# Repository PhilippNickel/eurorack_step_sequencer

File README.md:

# eurorack_step_sequencer
Open Hardware 8 Channel Eurorack Step Sequencer
# Introduction
These are the KiCad PCB files for a DIY eurorack 8 channel step sequencer module. The heart of the system is an Atmega16A and it features a small i2c OLED Display to modify certain settings. The manufacturing, firmware and testing are still work in progress, photos, videos and firmware will follow.
# 3d Model

# Schematic

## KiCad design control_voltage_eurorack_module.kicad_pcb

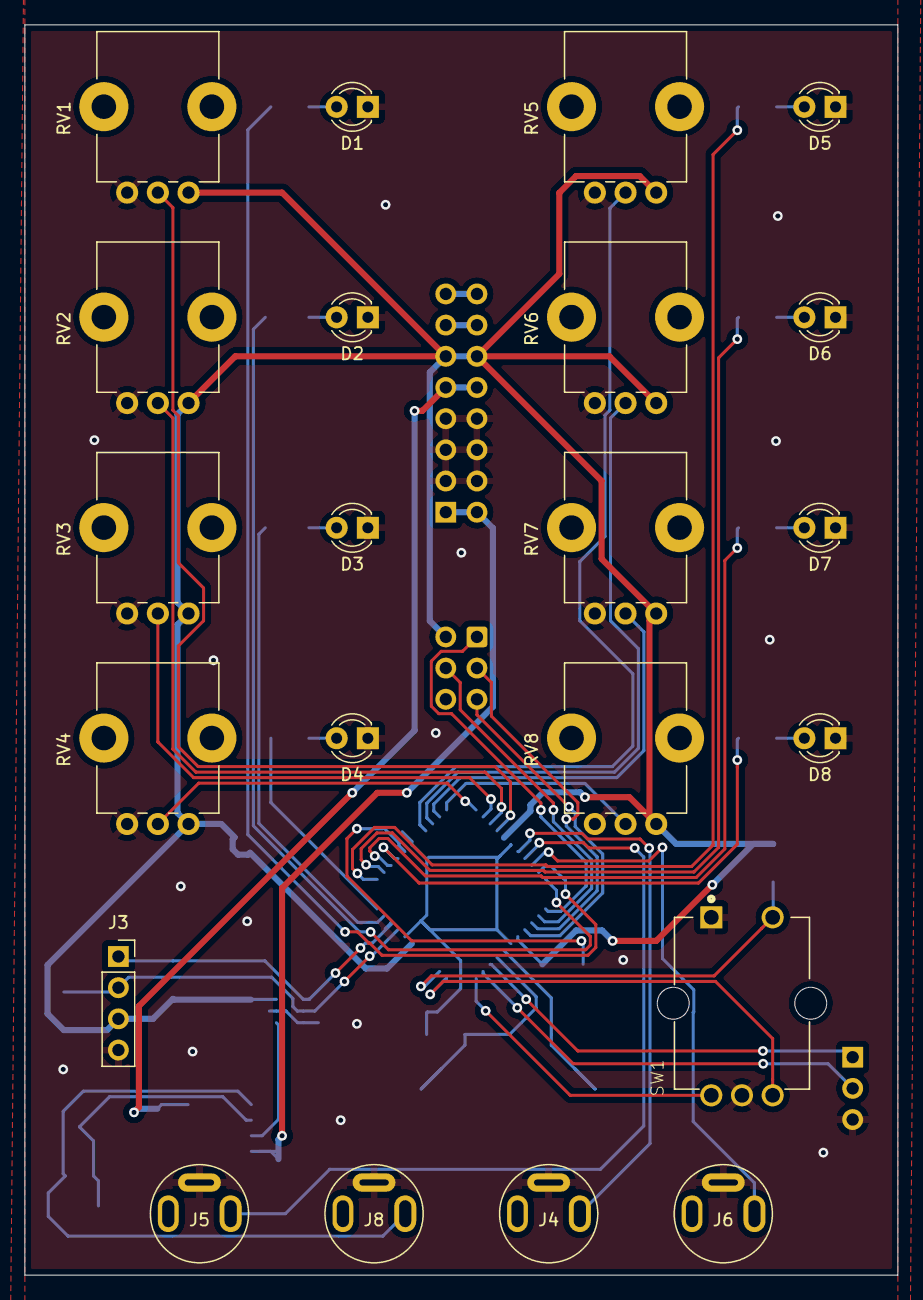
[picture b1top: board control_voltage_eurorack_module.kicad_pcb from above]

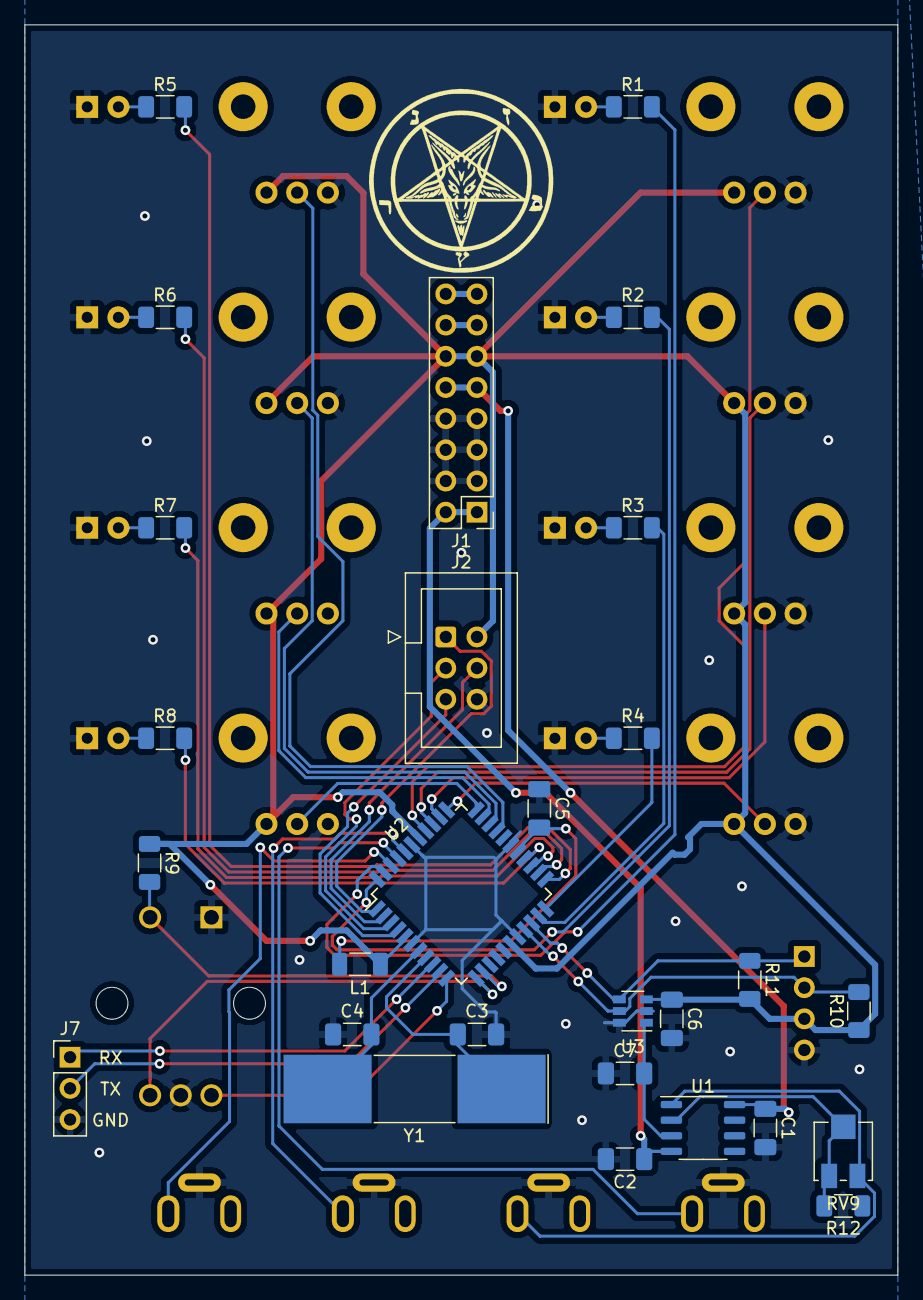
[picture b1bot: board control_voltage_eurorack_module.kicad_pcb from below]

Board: 2 copper layers, 71.1 x 101.9 mm, 50 parts (28 on the bottom side), 50 nets.

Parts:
C1, C2, C5, C6, C7: 100n; C_1206_3216Metric_Pad1.33x1.80mm_HandSolder
C3, C4: 20p; C_1206_3216Metric_Pad1.33x1.80mm_HandSolder
D1, D2, D3, D4, D5, D6, D7, D8: LED; LED_D3.0mm
J1: Conn_02x08_Odd_Even; PinHeader_2x08_P2.54mm_Vertical
J2: AVR-ISP-6; IDC-Header_2x03_P2.54mm_Vertical
J3: Conn_01x04; PinSocket_1x04_P2.54mm_Vertical
J4: TrigOut; Jack_3.5mm_VERTICAL
J5: GateOut; Jack_3.5mm_VERTICAL
J6: ExtClkIn; Jack_3.5mm_VERTICAL
J7: Conn_01x03; PinHeader_1x03_P2.54mm_Vertical
J8: CVOut; Jack_3.5mm_VERTICAL
L1: 10u; L_1206_3216Metric_Pad1.22x1.90mm_HandSolder
R1, R2, R3, R4, R5, R6, R7, R8: 200; R_1206_3216Metric_Pad1.30x1.75mm_HandSolder
R9, R10, R11: 10k; R_1206_3216Metric_Pad1.30x1.75mm_HandSolder
R12: 75k; R_1206_3216Metric_Pad1.30x1.75mm_HandSolder
RV1, RV2, RV3, RV4, RV5, RV6, RV7, RV8: R_POT; Potentiometer_Bourns_PTV09A-1_Single_Vertical
RV9: 100k; Potentiometer_Bourns_3314J_Vertical
SW1: Menu_Encoder; ENC_PEC12R-4025F-S0024
U1: TL072; SO-8_3.9x4.9mm_P1.27mm
U2: ATmega16A-AU; TQFP-44_10x10mm_P0.8mm
U3: MCP4725xxx-xCH; SOT-23-6
Y1: 16M; Crystal_SMD_SeikoEpson_MA505-2Pin_12.7x5.1mm_HandSoldering

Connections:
+5V: C6.1, J1.11, J1.12, J2.2, J3.3, L1.1, R9.1, R10.1, R11.2, RV1.1, RV2.1, RV3.1, RV4.1, RV5.1, RV6.1, RV7.1, RV8.1, U2.5, U2.17, U2.38, U3.3
+12V: C1.1, J1.9, J1.10, U1.8
-12V: C2.1, J1.1, J1.2, U1.4
CV: J1.15, J1.16
GND: C1.2, C2.2, C3.2, C4.2, C5.1, C6.2, C7.1, D1.1, D2.1, D3.1, D4.1, D5.1, D6.1, D7.1, D8.1, J1.3, J1.4, J1.5, J1.6, J1.7, J1.8, J2.6, J3.4, J4.S, J5.S, J6.S, J7.3, J8.S, R12.1, RV1.3, RV2.3, RV3.3, RV4.3, RV5.3, RV6.3, RV7.3, RV8.3, SW1.C, SW1.S1, U2.6, U2.18, U2.28, U2.39, U3.2, U3.6
Gate: J1.13, J1.14
LED0: R1.2, U2.43
LED1: R2.2, U2.44
LED2: R3.2, U2.21
LED3: R4.2, U2.22
LED4: R5.2, U2.23
LED5: R6.2, U2.24
LED6: R7.2, U2.25
LED7: R8.2, U2.26
MISO: J2.1, U2.1
MOSI: J2.4, U2.2
unnamed: C3.1, U2.8, Y1.1
unnamed: C4.1, U2.7, Y1.2
unnamed: C5.2, L1.2, U2.27
unnamed: C7.2, U1.3, U3.1
unnamed: D1.2, R1.1
unnamed: D2.2, R2.1
unnamed: D3.2, R3.1
unnamed: D4.2, R4.1
unnamed: D5.2, R5.1
unnamed: D6.2, R6.1
unnamed: D7.2, R7.1
unnamed: D8.2, R8.1
unnamed: J4.T, U2.40
unnamed: J5.T, U2.41
unnamed: J6.T, U2.42
unnamed: J8.T, RV9.3, U1.1
unnamed: R9.2, SW1.S2, U2.13
unnamed: R12.2, RV9.1, RV9.2, U1.2
unnamed: SW1.A, U2.11
unnamed: SW1.B, U2.12
Pot0: RV1.2, U2.37
Pot1: RV2.2, U2.36
Pot2: RV3.2, U2.35
Pot3: RV4.2, U2.34
Pot4: RV5.2, U2.30
Pot5: RV6.2, U2.31
Pot6: RV7.2, U2.32
Pot7: RV8.2, U2.33
RXD: J7.1, U2.9
Rst: J2.5, U2.4
SCK: J2.3, U2.3
SCL: J3.2, R10.2, U2.19, U3.5
SDA: J3.1, R11.1, U2.20, U3.4
TXD: J7.2, U2.10

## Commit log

2021-03-23 removed .zip from repo
2021-03-28 fixed wrong i2c pins and added uart port
2021-03-28 added 3d shapes
2021-04-02 added pic of 3dmodel
2021-04-02 fixed filename
2022-03-31 updated to kicad 6
2022-05-17 added schematic
